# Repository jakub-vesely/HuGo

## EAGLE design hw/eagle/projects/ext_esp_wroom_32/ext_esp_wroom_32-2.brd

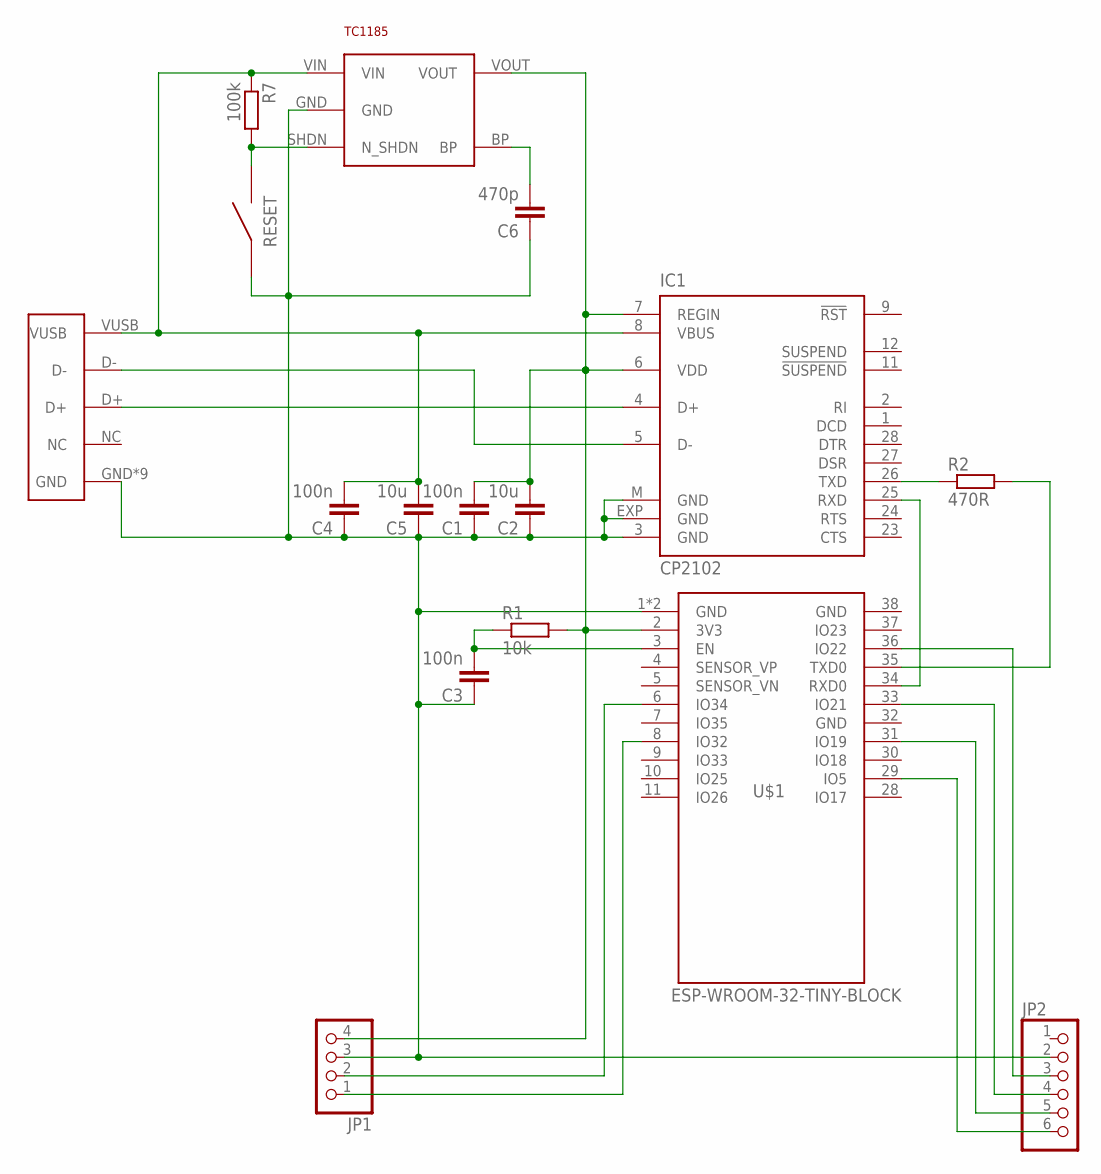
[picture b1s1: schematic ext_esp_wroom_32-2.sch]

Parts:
C1, C3, C4: 100n; C0805K
C2, C5: 10u; C0805K
C6: 470p; C0805K
IC1: CP2102; MLP28
JP1: PINHD-1X4; 1X04
JP2: PINHD-1X6; 1X06
R1: 10k; R0805
R2: 470R; R0805
R7: 100k; R0603
RESET: BYTTON-B3U; BUTTON-B3U
TC1185: TC1185; SOT32-5
U$1: ESP-WROOM-32-TINY-BLOCK
USB: USBMICRO; MICROUSB-MOLEX

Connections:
EN: C3.2, R1.1, U$1.3 (EN)
GND: C1.1, C2.1, C3.1, C4.1, C5.1, C6.1, IC1.3 (GND), IC1.EXP (GND), IC1.M (GND), JP1.3, JP2.2, RESET.P$1, TC1185.GND, U$1.1 (GND), U$1.32 (GND), U$1.38 (GND), U$1.GND, USB.GND, USB.GND1 (GND), USB.GND2 (GND), USB.GND3 (GND), USB.GND4 (GND), USB.P$1 (GND), USB.P$2 (GND), USB.P$3 (GND), USB.P$6 (GND)
unnamed: IC1.5 (D-), USB.D-
unnamed: IC1.4 (D+), USB.D+
unnamed: IC1.26 (TXD), R2.1
unnamed: R2.2, U$1.35 (TXD0)
unnamed: IC1.25 (RXD), U$1.34 (RXD0)
unnamed: C6.2, TC1185.BP
unnamed: C4.2, C5.2, IC1.8 (VBUS), R7.1, TC1185.VIN, USB.VUSB
unnamed: R7.2, RESET.P$2, TC1185.SHDN (N_SHDN)
P0: JP1.2, U$1.6 (IO34)
P1: JP1.1, U$1.8 (IO32)
P4: JP2.3, U$1.36 (IO22)
SCL: JP2.5, U$1.31 (IO19)
SDA: JP2.6, U$1.29 (IO5)
UPDI: JP2.4, U$1.33 (IO21)
VCC: C1.2, C2.2, IC1.6 (VDD), IC1.7 (REGIN), JP1.4, R1.2, TC1185.VOUT, U$1.2 (3V3)

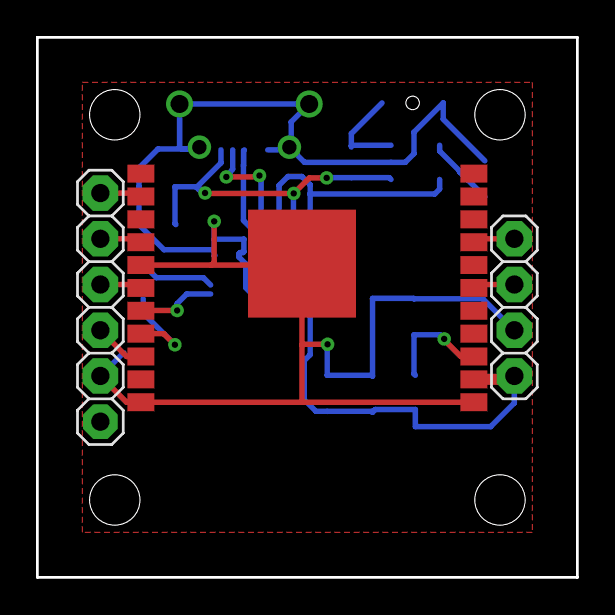
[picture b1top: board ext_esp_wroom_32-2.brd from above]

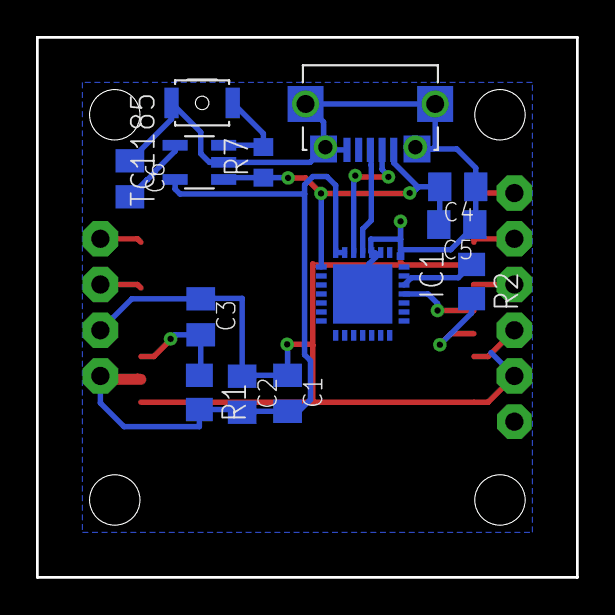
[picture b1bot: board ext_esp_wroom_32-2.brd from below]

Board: 2 copper layers, 30.0 x 30.0 mm, 16 parts (13 on the bottom side), 17 nets.

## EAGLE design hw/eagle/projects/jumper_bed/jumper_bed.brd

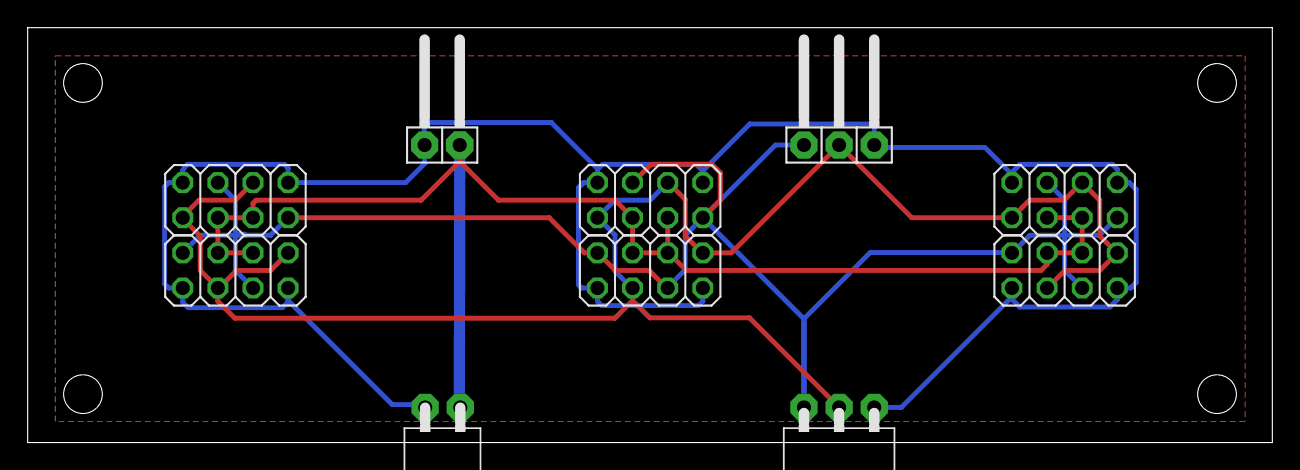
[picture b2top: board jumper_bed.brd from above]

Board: 2 copper layers, 90.0 x 30.0 mm, 10 parts (0 on the bottom side), 4 nets.

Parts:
JP1, JP2, JP3, JP4, JP5, JP6: 2X04
JP7: 1X02/90
JP8: 1X03/90
JP9: 1X03/90F
JP10: 1X02/90F

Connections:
GND: JP1.1, JP1.7, JP2.2, JP2.8, JP3.1, JP3.7, JP4.2, JP4.8, JP5.1, JP5.7, JP6.2, JP6.8, JP7.1, JP8.3, JP9.1, JP10.2
SCL: JP1.2, JP1.5, JP2.4, JP2.7, JP3.2, JP3.5, JP4.4, JP4.7, JP5.2, JP5.5, JP6.4, JP6.7, JP8.1, JP9.3
SDA: JP1.3, JP1.8, JP2.1, JP2.6, JP3.3, JP3.8, JP4.1, JP4.6, JP5.3, JP5.8, JP6.1, JP6.6, JP8.2, JP9.2
VCC: JP1.4, JP1.6, JP2.3, JP2.5, JP3.4, JP3.6, JP4.3, JP4.5, JP5.4, JP5.6, JP6.3, JP6.5, JP7.2, JP10.1

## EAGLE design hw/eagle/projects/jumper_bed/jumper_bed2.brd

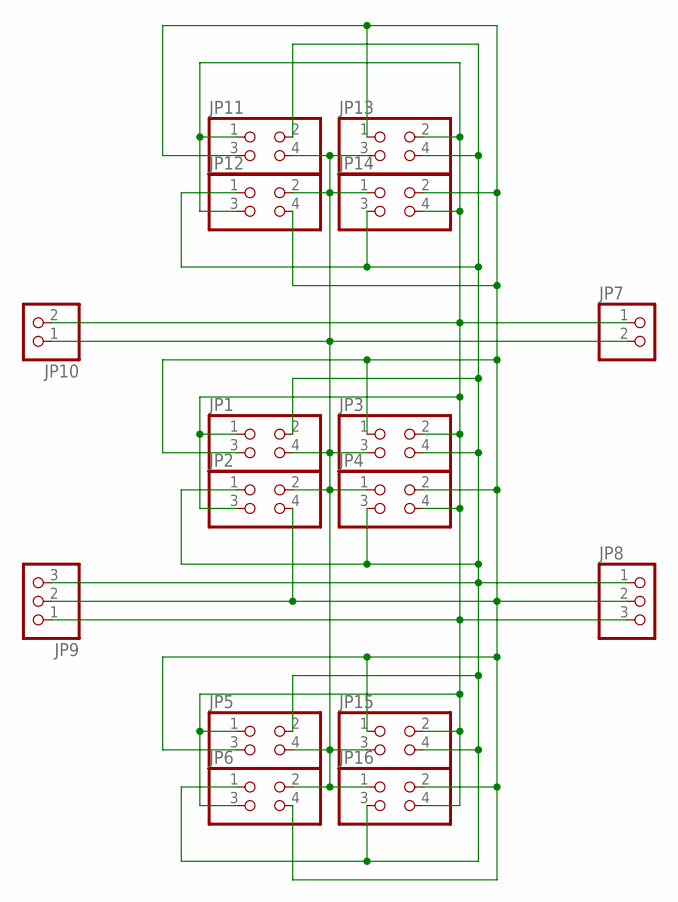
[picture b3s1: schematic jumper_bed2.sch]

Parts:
JP1, JP2, JP3, JP4, JP5, JP6, JP11, JP12, JP13, JP14, JP15, JP16: PINHD-2X2; 2X02
JP7: PINHD-1X2/90; 1X02/90
JP8: PINHD-1X3/90; 1X03/90
JP9: PINHD-1X31X03/90F; 1X03/90F
JP10: PINHD-1X21X02/90F; 1X02/90F

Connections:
GND: JP1.1, JP2.3, JP3.2, JP4.4, JP5.1, JP6.3, JP7.1, JP8.3, JP9.1, JP10.2, JP11.1, JP12.3, JP13.2, JP14.4, JP15.2, JP16.4
SCL: JP1.2, JP2.1, JP3.4, JP4.3, JP5.2, JP6.1, JP8.1, JP9.3, JP11.2, JP12.1, JP13.4, JP14.3, JP15.4, JP16.3
SDA: JP1.3, JP2.4, JP3.1, JP4.2, JP5.3, JP6.4, JP8.2, JP9.2, JP11.3, JP12.4, JP13.1, JP14.2, JP15.1, JP16.2
VCC: JP1.4, JP2.2, JP3.3, JP4.1, JP5.4, JP6.2, JP7.2, JP10.1, JP11.4, JP12.2, JP13.3, JP14.1, JP15.3, JP16.1

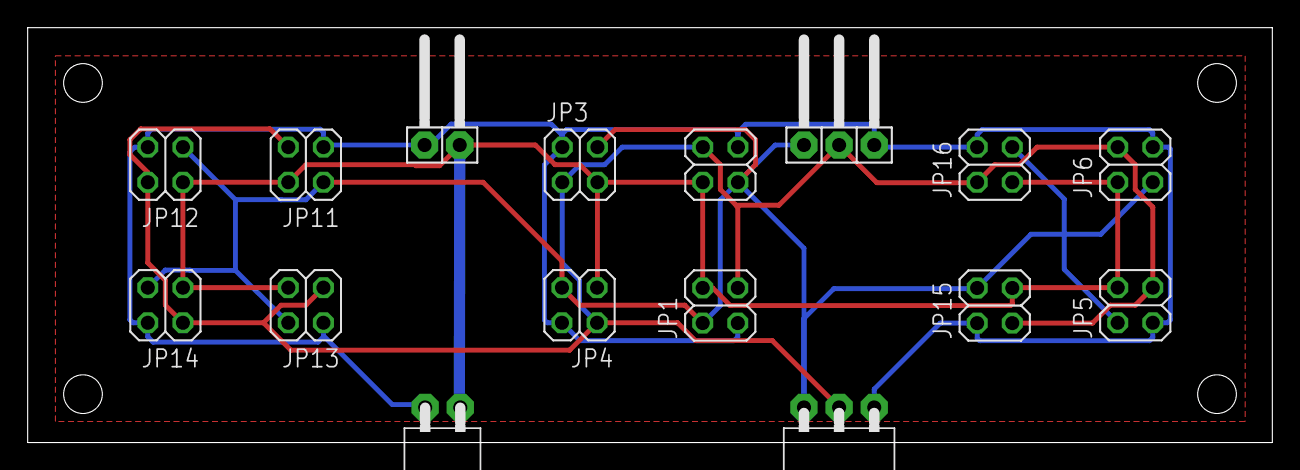
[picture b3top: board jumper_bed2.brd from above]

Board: 2 copper layers, 90.0 x 30.0 mm, 16 parts (0 on the bottom side), 4 nets.

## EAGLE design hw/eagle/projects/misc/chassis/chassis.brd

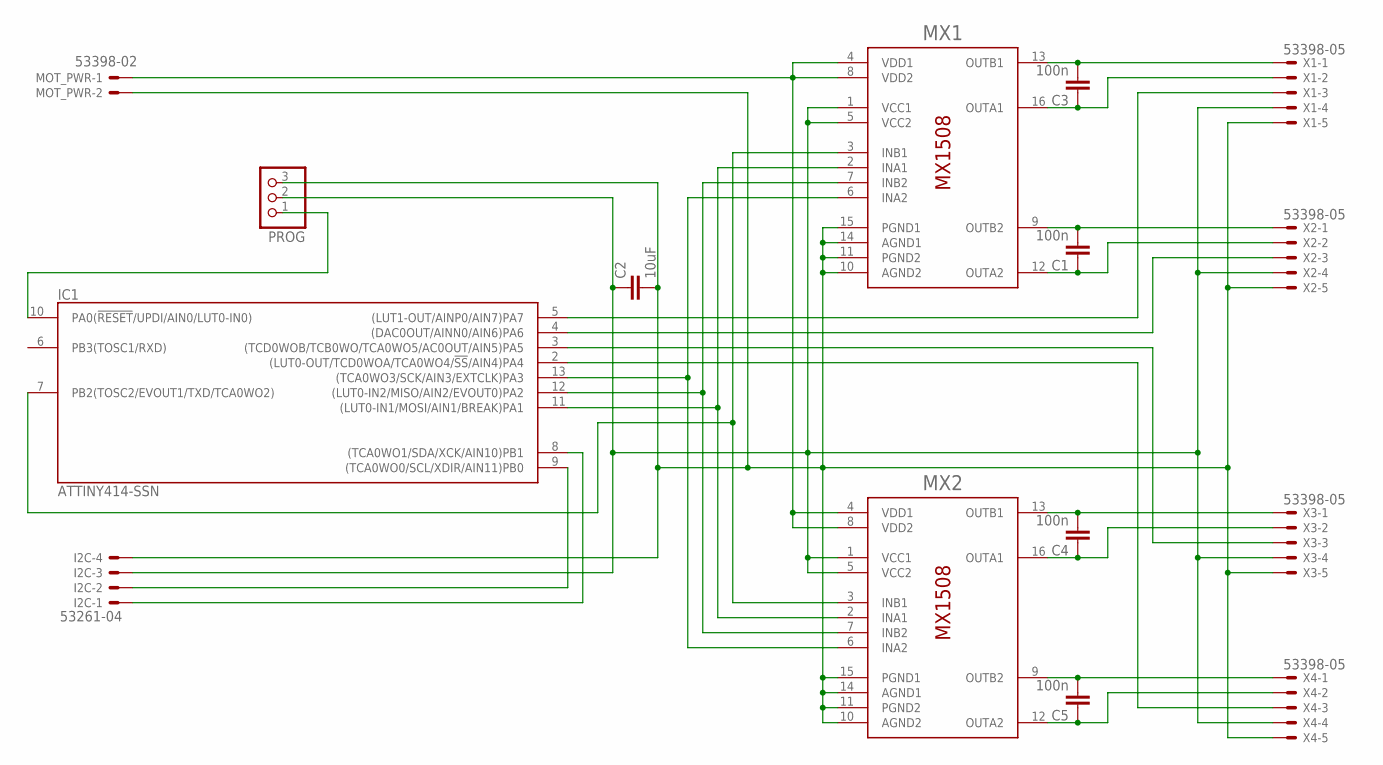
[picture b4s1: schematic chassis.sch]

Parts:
C1, C3, C4, C5: 100n; C0805K
C2: 10uF; C0805K
I2C: 53261-04
IC1: ATTINY414-SSN; SO14
MOT_PWR: 53398-02
MX1, MX2: MX1508; SOP16
PROG: PINHD-1X3/90; 1X03/90
X1, X2, X3, X4: 53398-05

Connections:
GND: C2.2, I2C.4, IC1.14 (GND), MOT_PWR.2, MX1.10 (AGND2), MX1.11 (PGND2), MX1.14 (AGND1), MX1.15 (PGND1), MX2.10 (AGND2), MX2.11 (PGND2), MX2.14 (AGND1), MX2.15 (PGND1), PROG.3, X1.5, X2.5, X3.5, X4.5
unnamed: C3.2, MX1.13 (OUTB1), X1.1
unnamed: C3.1, MX1.16 (OUTA1), X1.2
unnamed: C1.2, MX1.9 (OUTB2), X2.1
unnamed: C1.1, MX1.12 (OUTA2), X2.2
unnamed: C4.2, MX2.13 (OUTB1), X3.1
unnamed: C4.1, MX2.16 (OUTA1), X3.2
unnamed: C5.2, MX2.9 (OUTB2), X4.1
unnamed: C5.1, MX2.12 (OUTA2), X4.2
unnamed: IC1.5 ((LUT1-OUT/AINP0/AIN7)PA7), X1.3
unnamed: IC1.4 ((DAC0OUT/AINN0/AIN6)PA6), X2.3
unnamed: IC1.2 ((LUT0-OUT/TCD0WOA/TCA0WO4/!SS!/AIN4)PA4), X4.3
unnamed: IC1.3 ((TCD0WOB/TCB0WO/TCA0WO5/AC0OUT/AIN5)PA5), X3.3
unnamed: IC1.7 (PB2(TOSC2/EVOUT1/TXD/TCA0WO2)), MX1.3 (INB1), MX2.3 (INB1)
unnamed: IC1.11 ((LUT0-IN1/MOSI/AIN1/BREAK)PA1), MX1.2 (INA1), MX2.2 (INA1)
unnamed: IC1.12 ((LUT0-IN2/MISO/AIN2/EVOUT0)PA2), MX1.7 (INB2), MX2.7 (INB2)
unnamed: IC1.13 ((TCA0WO3/SCK/AIN3/EXTCLK)PA3), MX1.6 (INA2), MX2.6 (INA2)
unnamed: I2C.2, IC1.9 ((TCA0WO0/SCL/XDIR/AIN11)PB0)
unnamed: I2C.1, IC1.8 ((TCA0WO1/SDA/XCK/AIN10)PB1)
unnamed: IC1.10 (PA0(!RESET!/UPDI/AIN0/LUT0-IN0)), PROG.1
VCC: C2.1, I2C.3, IC1.1 (VCC), MX1.1 (VCC1), MX1.5 (VCC2), MX2.1 (VCC1), MX2.5 (VCC2), PROG.2, X1.4, X2.4, X3.4, X4.4
VDD: MOT_PWR.1, MX1.4 (VDD1), MX1.8 (VDD2), MX2.4 (VDD1), MX2.8 (VDD2)

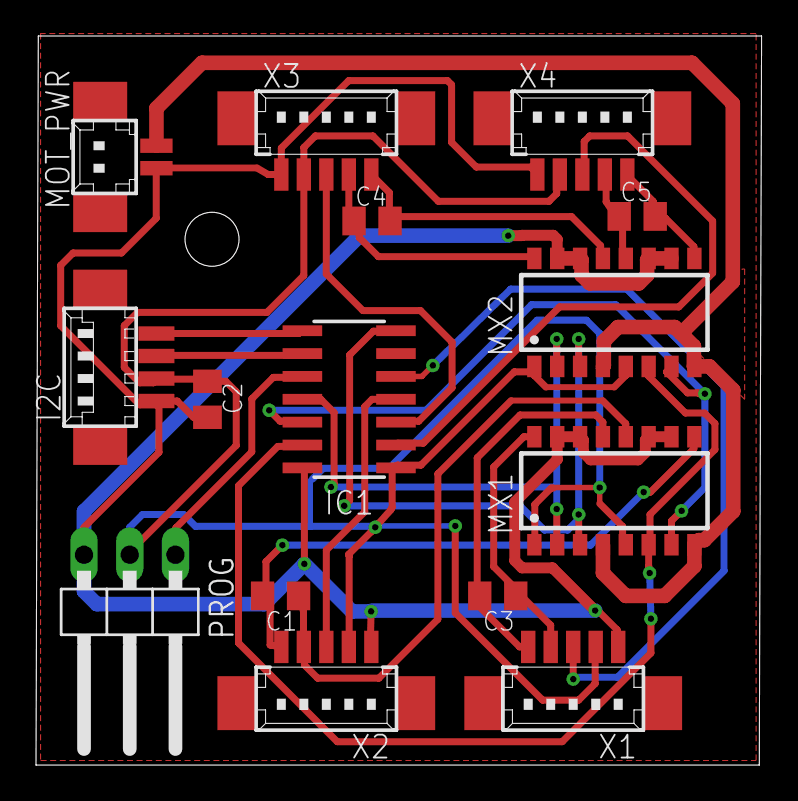
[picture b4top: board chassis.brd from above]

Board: 2 copper layers, 40.3 x 40.5 mm, 15 parts (0 on the bottom side), 22 nets.

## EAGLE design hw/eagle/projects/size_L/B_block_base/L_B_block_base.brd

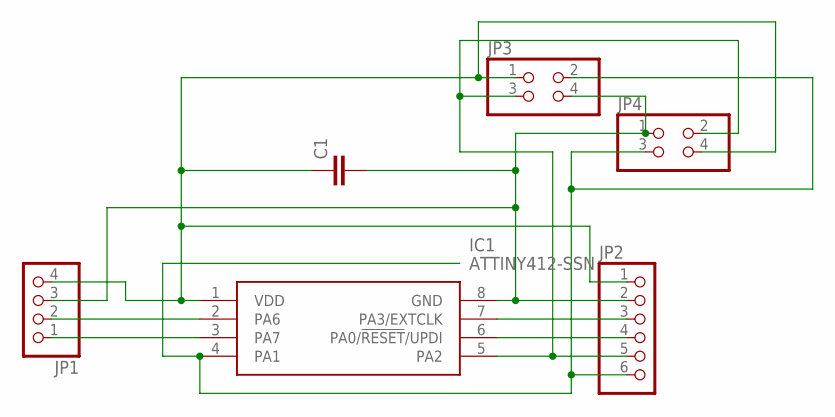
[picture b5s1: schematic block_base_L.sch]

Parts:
C1: C-EUC0805K; C0805K
IC1: ATTINY412-SSN; SOIC127P600X175-8N
JP1: PINHD-1X4; 1X04
JP2: PINHD-1X6; 1X06
JP3, JP4: PINHD-2X2; 2X02

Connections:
GND: C1.2, IC1.8 (GND), JP1.3, JP2.2, JP3.4, JP4.1
P0: IC1.2 (PA6), JP1.2
P1: IC1.3 (PA7), JP1.1
P4: IC1.7 (PA3/EXTCLK), JP2.3
SCL: IC1.5 (PA2), JP2.5, JP3.3, JP4.2
SDA: IC1.4 (PA1), JP2.6, JP3.2, JP4.3
UPDI: IC1.6 (PA0/!RESET!/UPDI), JP2.4
VDD: C1.1, IC1.1 (VDD), JP1.4, JP2.1, JP3.1, JP4.4

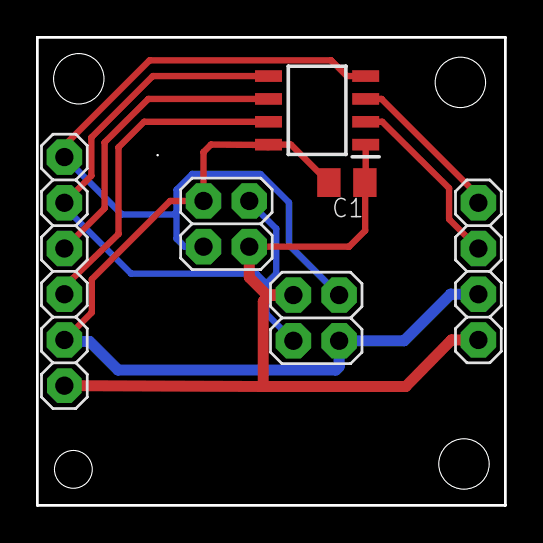
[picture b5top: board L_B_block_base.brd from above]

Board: 2 copper layers, 26.0 x 26.0 mm, 6 parts (0 on the bottom side), 8 nets.

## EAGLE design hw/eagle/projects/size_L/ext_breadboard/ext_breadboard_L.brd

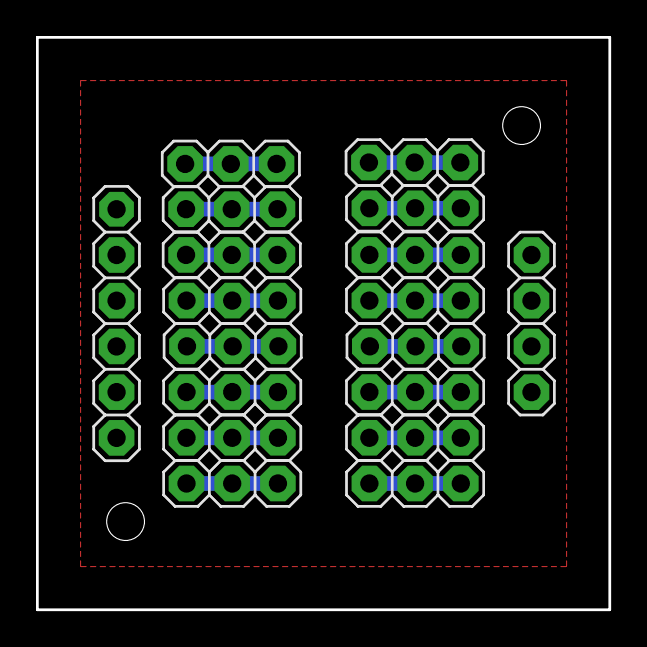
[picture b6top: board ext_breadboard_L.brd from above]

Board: 2 copper layers, 31.8 x 31.8 mm, 18 parts (0 on the bottom side), 18 nets.

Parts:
JP1: 1X04
JP2: 1X06
JP3, JP4, JP5, JP6, JP7, JP8, JP9, JP10, JP11, JP12, JP13, JP14, JP15, JP16, JP17, JP18: 1X03

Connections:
GND: JP1.2, JP2.5
unnamed: JP17.1, JP17.2, JP17.3
unnamed: JP15.1, JP15.2, JP15.3
unnamed: JP13.1, JP13.2, JP13.3
unnamed: JP11.1, JP11.2, JP11.3
unnamed: JP9.1, JP9.2, JP9.3
unnamed: JP7.1, JP7.2, JP7.3
unnamed: JP5.1, JP5.2, JP5.3
unnamed: JP3.1, JP3.2, JP3.3
unnamed: JP4.1, JP4.2, JP4.3
unnamed: JP6.1, JP6.2, JP6.3
unnamed: JP8.1, JP8.2, JP8.3
unnamed: JP10.1, JP10.2, JP10.3
unnamed: JP12.1, JP12.2, JP12.3
unnamed: JP14.1, JP14.2, JP14.3
unnamed: JP16.1, JP16.2, JP16.3
unnamed: JP18.1, JP18.2, JP18.3
VDD: JP1.1, JP2.6

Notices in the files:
parts and their libraries:
esp32: Creative Commons Attribution-ShareAlike 4.0 International
